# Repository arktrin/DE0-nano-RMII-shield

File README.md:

# DE0-nano_RMII
DE0-nano RMII shield

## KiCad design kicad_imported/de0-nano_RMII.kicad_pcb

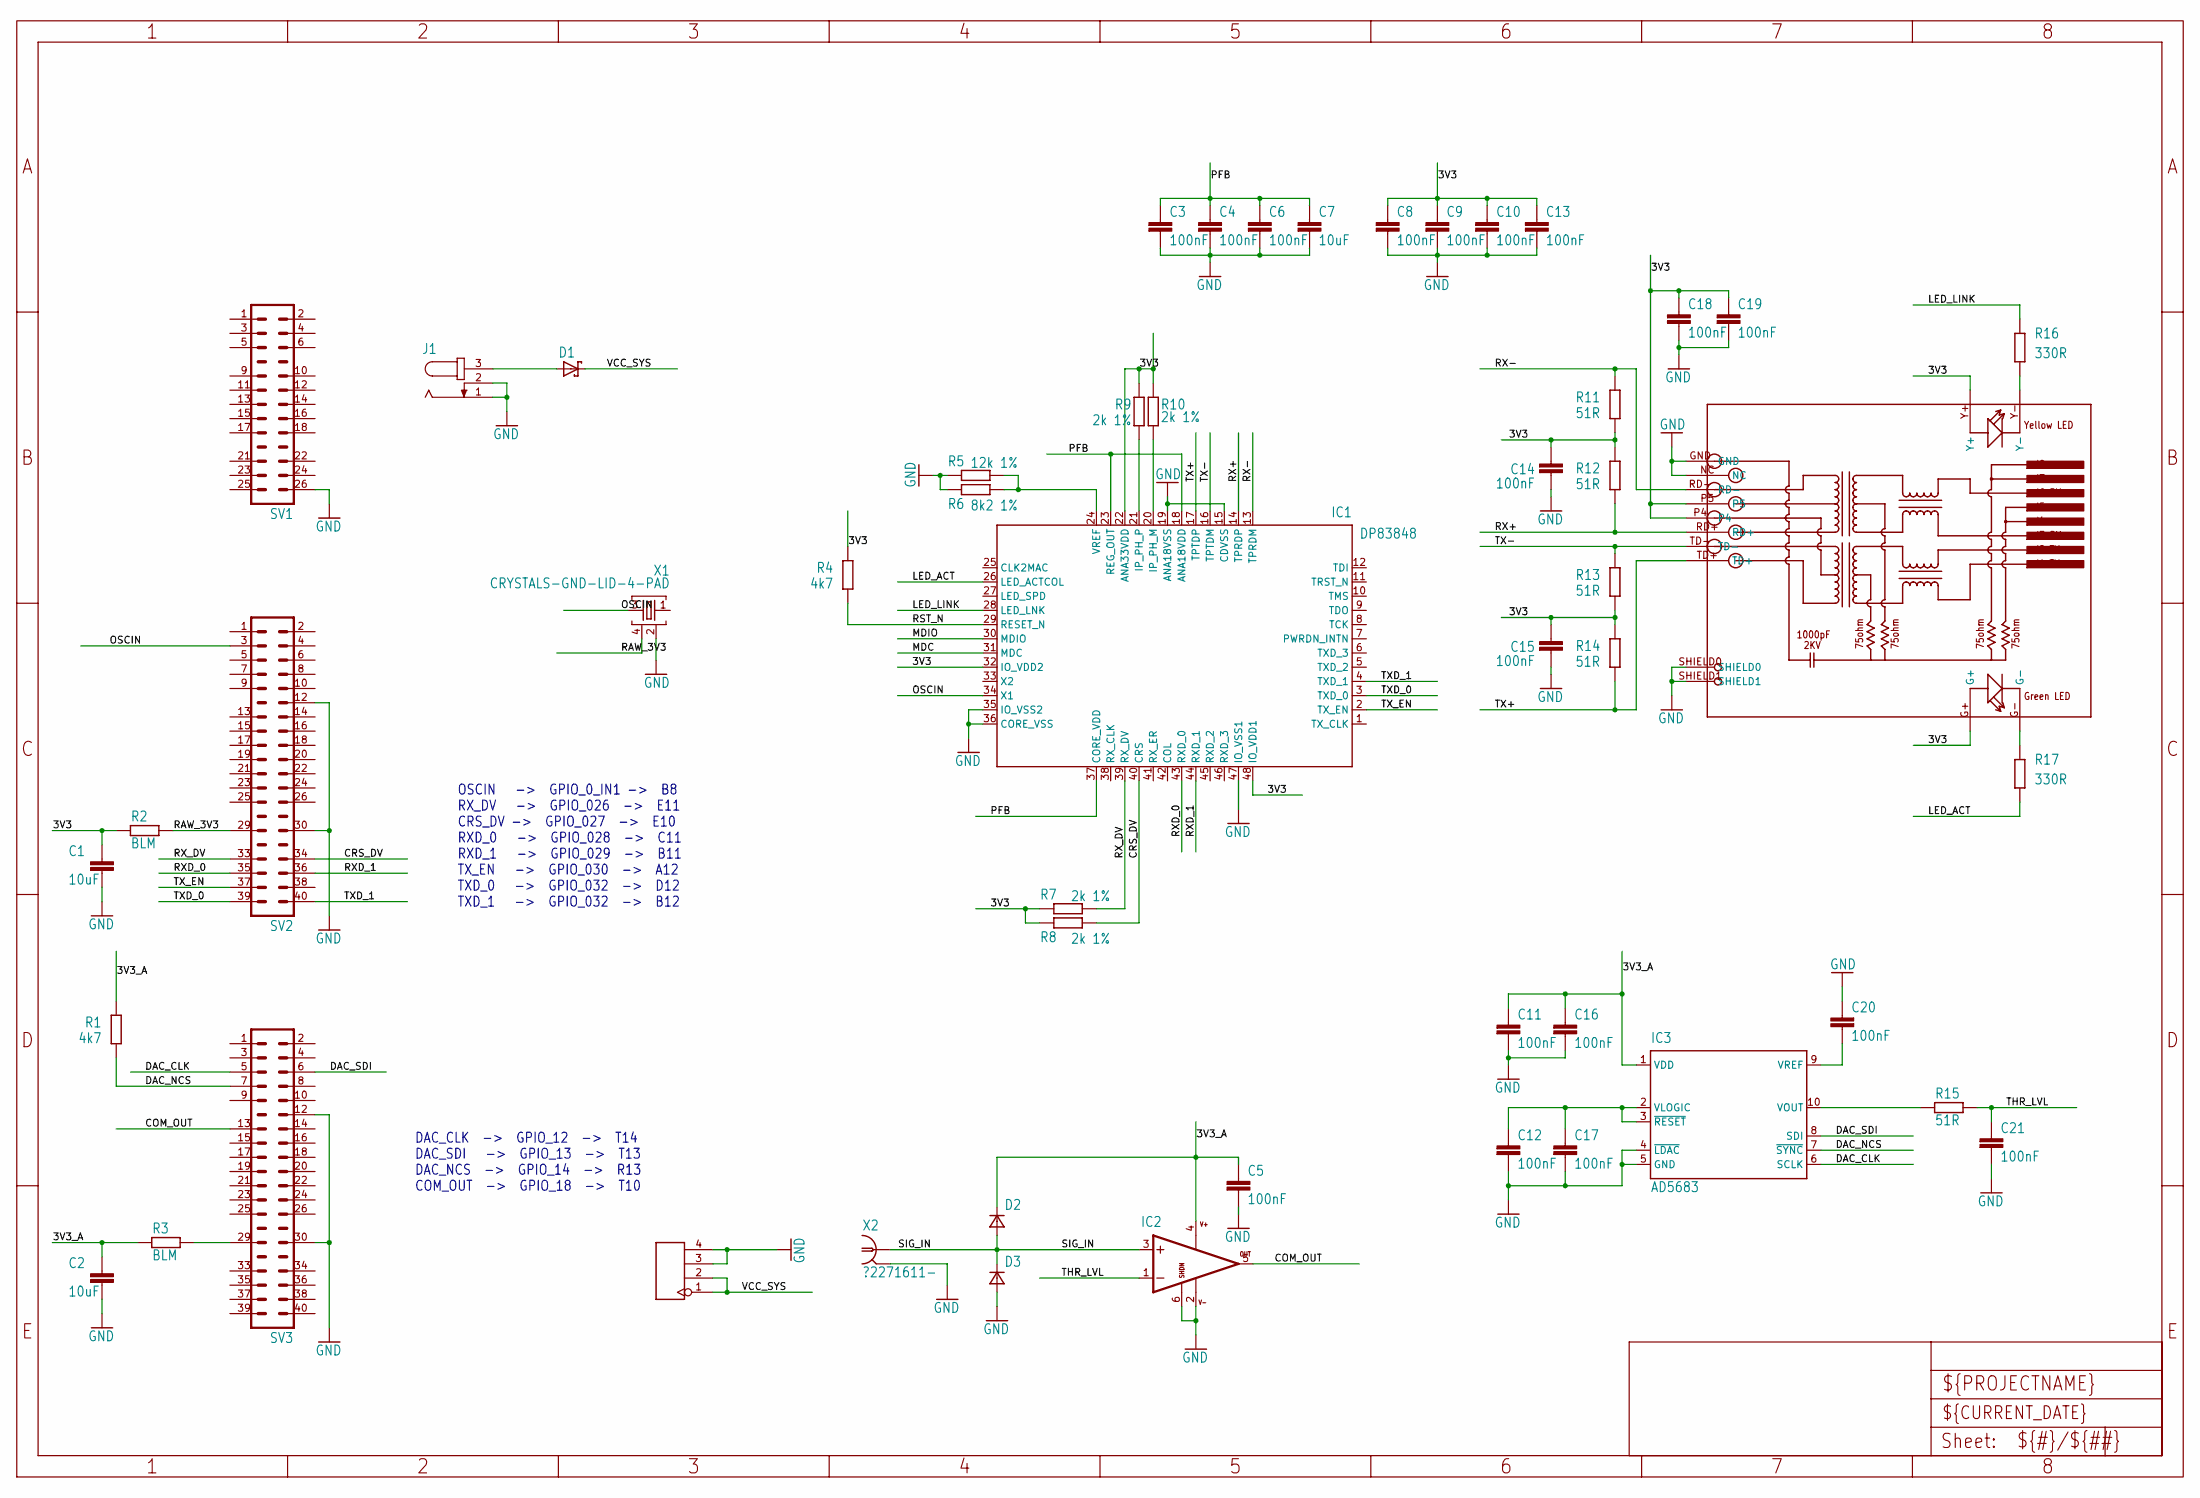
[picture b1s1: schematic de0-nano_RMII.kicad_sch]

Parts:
C1, C2, C7: 10uF; C0805
C3, C4, C5, C6, C8, C9, C10, C11, C12, C13, C14, C15, C16, C17, C18, C19, C20, C21: 100nF; C0603
D1: SCHOTTKY-DIODESMC; SMC
D2, D3: DSOD323; SOD323
IC1: DP83848; LQFP48
IC2: LT1719; TSOT23-6
IC3: AD5683; SO10
J1: JACK-PLUG1; SPC4078
J2: HEADER-4P-60/35MIL; 4P-65_35MIL
J3: RJ45-HR911105A-HR911105A; RJ45
R1, R4: 4k7; R0603
R2, R3: BLM; R0603
R5: 12k 1%; R0603
R6: 8k2 1%; R0603
R7, R8, R9, R10: 2k 1%; R0603
R11, R12, R13, R14, R15: 51R; R0603
R16, R17: 330R; R0603
SV1: MA13-2_ALT
SV2, SV3: MA20-2_ALT
X1: CRYSTALS-GND-LID-4-PAD; 7.5X5-4-PAD
X2: ?2271611-; AMP_227161

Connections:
3V3: C1.1, C8.1, C9.1, C10.1, C13.1, C14.1, C15.1, C18.1, C19.1, IC1.22 (ANA33VDD), IC1.32 (IO_VDD2), IC1.48 (IO_VDD1), J3.G+, J3.P4, J3.P5, J3.Y+, R2.1, R4.1, R7.2, R8.2, R9.2, R10.2, R11.2, R12.1, R13.2, R14.1
3V3_A: C2.1, C5.1, C11.1, C16.1, D2.1 (C), IC2.4 (V+), IC3.1 (VDD), R1.1, R3.1
COM_OUT: IC2.5 (OUT), SV3.13
CRS_DV: IC1.40 (CRS), R8.1, SV2.34
DAC_CLK: IC3.6 (SCLK), SV3.5
DAC_NCS: IC3.7 (~SYNC), R1.2, SV3.7
DAC_SDI: IC3.8 (SDI), SV3.6
GND: C1.2, C2.2, C3.2, C4.2, C5.2, C6.2, C7.2, C8.2, C9.2, C10.2, C11.2, C12.2, C13.2, C14.2, C15.2, C16.2, C17.2, C18.2, C19.2, C20.2, C21.2, D3.2 (A), IC1.15 (CDVSS), IC1.19 (ANA18VSS), IC1.35 (IO_VSS2), IC1.36 (CORE_VSS), IC1.47 (IO_VSS1), IC2.2 (V-), IC2.6 (SHDN), IC3.4 (~LDAC), IC3.5 (GND), J1.1, J1.2, J2.3, J2.4, J3.GND, J3.NC, J3.SHIELD0, J3.SHIELD1, R5.2, R6.2, SV1.26, SV2.12, SV2.30, SV3.12, SV3.30, X1.2, X2.2
LED_ACT: IC1.26 (LED_ACTCOL), R17.1
LED_LINK: IC1.28 (LED_LNK), R16.2
MDC: IC1.31 (MDC)
MDIO: IC1.30 (MDIO)
unnamed: R3.2, SV3.29
unnamed: IC1.21 (IP_PH_P), R9.1
unnamed: J3.Y-, R16.1
unnamed: IC1.20 (IP_PH_M), R10.1
unnamed: J3.G-, R17.2
unnamed: IC3.10 (VOUT), R15.1
unnamed: IC1.24 (VREF), R5.1, R6.1
unnamed: C20.1, IC3.9 (VREF)
OSCIN: IC1.34 (X1), SV2.3, X1.3
PFB: C3.1, C4.1, C6.1, C7.1, IC1.18 (ANA18VDD), IC1.23 (REG_OUT), IC1.37 (CORE_VDD)
RAW_3V3: R2.2, SV2.29, X1.4
RST_N: IC1.29 (RESET_N), R4.2
RX+: IC1.14 (TPRDP), J3.RD+, R12.2
RX-: IC1.13 (TPRDM), J3.RD-, R11.1
RXD_0: IC1.43 (RXD_0), SV2.35
RXD_1: IC1.44 (RXD_1), SV2.36
RX_DV: IC1.39 (RX_DV), R7.1, SV2.33
SIG_IN: D2.2 (A), D3.1 (C), IC2.3 (+IN), X2.1
THR_LVL: C21.1, IC2.1 (-IN), R15.2
TX+: IC1.17 (TPTDP), J3.TD+, R14.2
TX-: IC1.16 (TPTDM), J3.TD-, R13.1
TXD_0: IC1.3 (TXD_0), SV2.39
TXD_1: IC1.4 (TXD_1), SV2.40
TX_EN: IC1.2 (TX_EN), SV2.37
VCC_SYS: D1.C, J2.1, J2.2
VLOGIC: C12.1, C17.1, IC3.2 (VLOGIC), IC3.3 (~RESET)
V_RAW: D1.A, J1.3

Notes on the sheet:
DAC_CLK -> GPIO_12 -> T14 DAC_SDI -> GPIO_13 -> T13 DAC_NCS -> GPIO_14 -> R13 COM_OUT -> GPIO_18 -> T10
OSCIN -> GPIO_0_IN1 -> B8 RX_DV -> GPIO_026 -> E11 CRS_DV -> GPIO_027 -> E10 RXD_0 -> GPIO_028 -> C11 RXD_1 -> GPIO_029 -> B11 TX_EN -> GPIO_030 -> A12 TXD_0 -> GPIO_032 -> D12 TXD_1 -> GPIO_032 -> B12

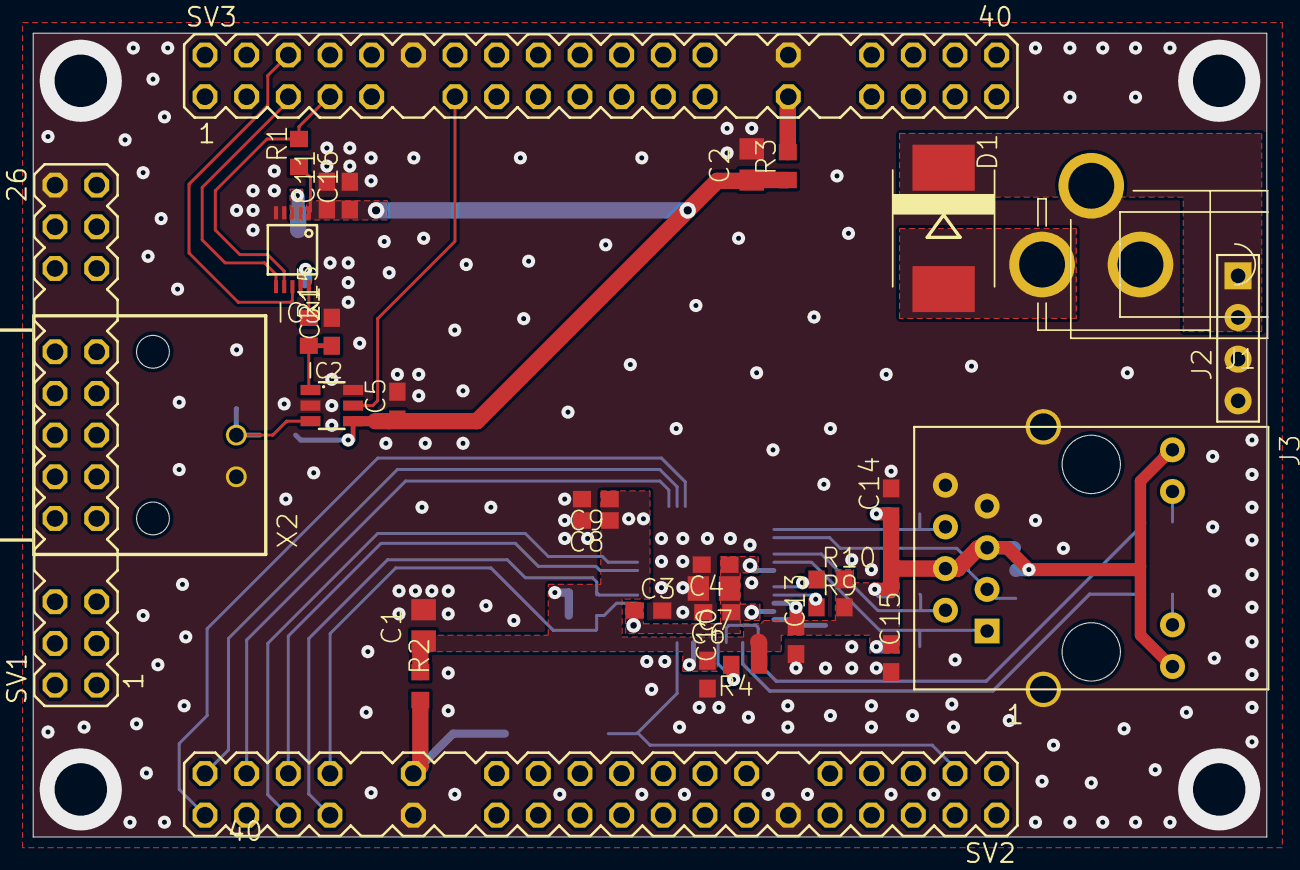
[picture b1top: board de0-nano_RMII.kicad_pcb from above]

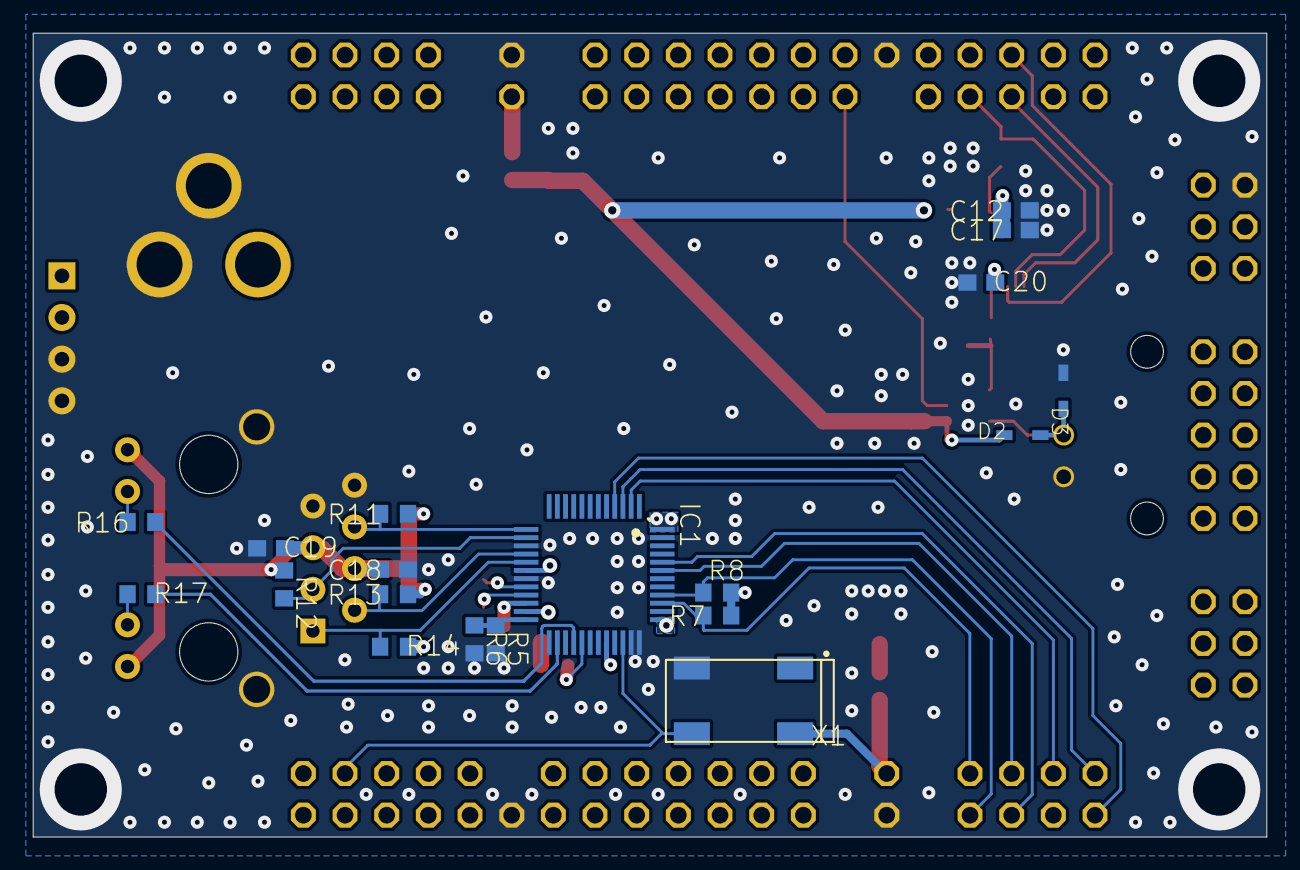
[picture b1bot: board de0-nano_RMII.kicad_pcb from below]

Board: 2 copper layers, 75.2 x 49.0 mm, 52 parts (19 on the bottom side), 37 nets.

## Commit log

2017-02-26 real initial commit
2017-02-26 almost done
2017-02-27 RX_DV and CRS_DV added
2017-03-01 test branch
2017-03-01 removed some pads on connector
2017-03-02 added external power and DAC
2017-03-07 added protection diodes at the input, and separate crystal oscillator
2017-03-08 gerber generated
2023-09-02 add schematics in pdf
    its been a while [:
2023-09-02 abandon eagle, move to kicad
2023-09-02 fix kicad files location
2023-09-02 unhide LT1719 comparator name in schematics
